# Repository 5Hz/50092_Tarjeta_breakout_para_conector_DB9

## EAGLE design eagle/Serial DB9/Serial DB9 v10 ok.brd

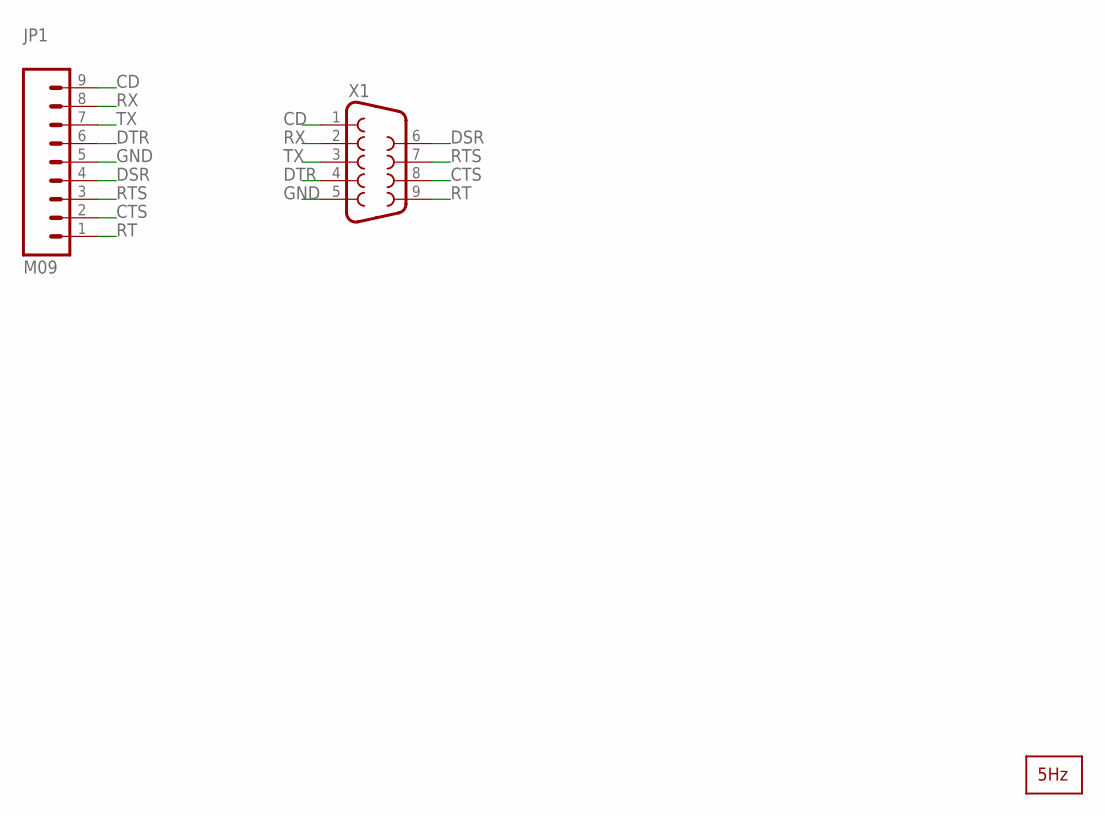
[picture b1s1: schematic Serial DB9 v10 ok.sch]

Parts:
JP1: M09; 1X09
U$1: LOGO2_SILK10MM; LOGO2_10MM
X1: DB9FEMALE; DB9

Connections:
CD: JP1.9, X1.1
CTS: JP1.2, X1.8
DSR: JP1.4, X1.6
DTR: JP1.6, X1.4
GND: JP1.5, X1.5
RT: JP1.1, X1.9
RTS: JP1.3, X1.7
RX: JP1.8, X1.2
TX: JP1.7, X1.3

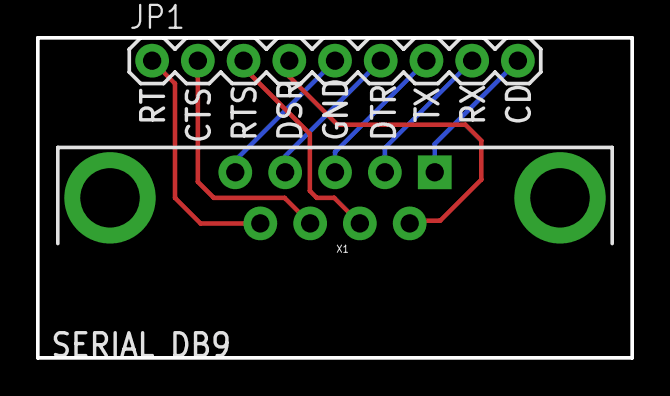
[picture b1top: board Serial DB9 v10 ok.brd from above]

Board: 2 copper layers, 33.0 x 17.8 mm, 3 parts (1 on the bottom side), 9 nets.

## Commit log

2014-01-13 creación

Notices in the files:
parts and their libraries:
SparkFun: Licensing: CC v3.0 Share-Alike You are welcome to use this library for commercial purposes.
